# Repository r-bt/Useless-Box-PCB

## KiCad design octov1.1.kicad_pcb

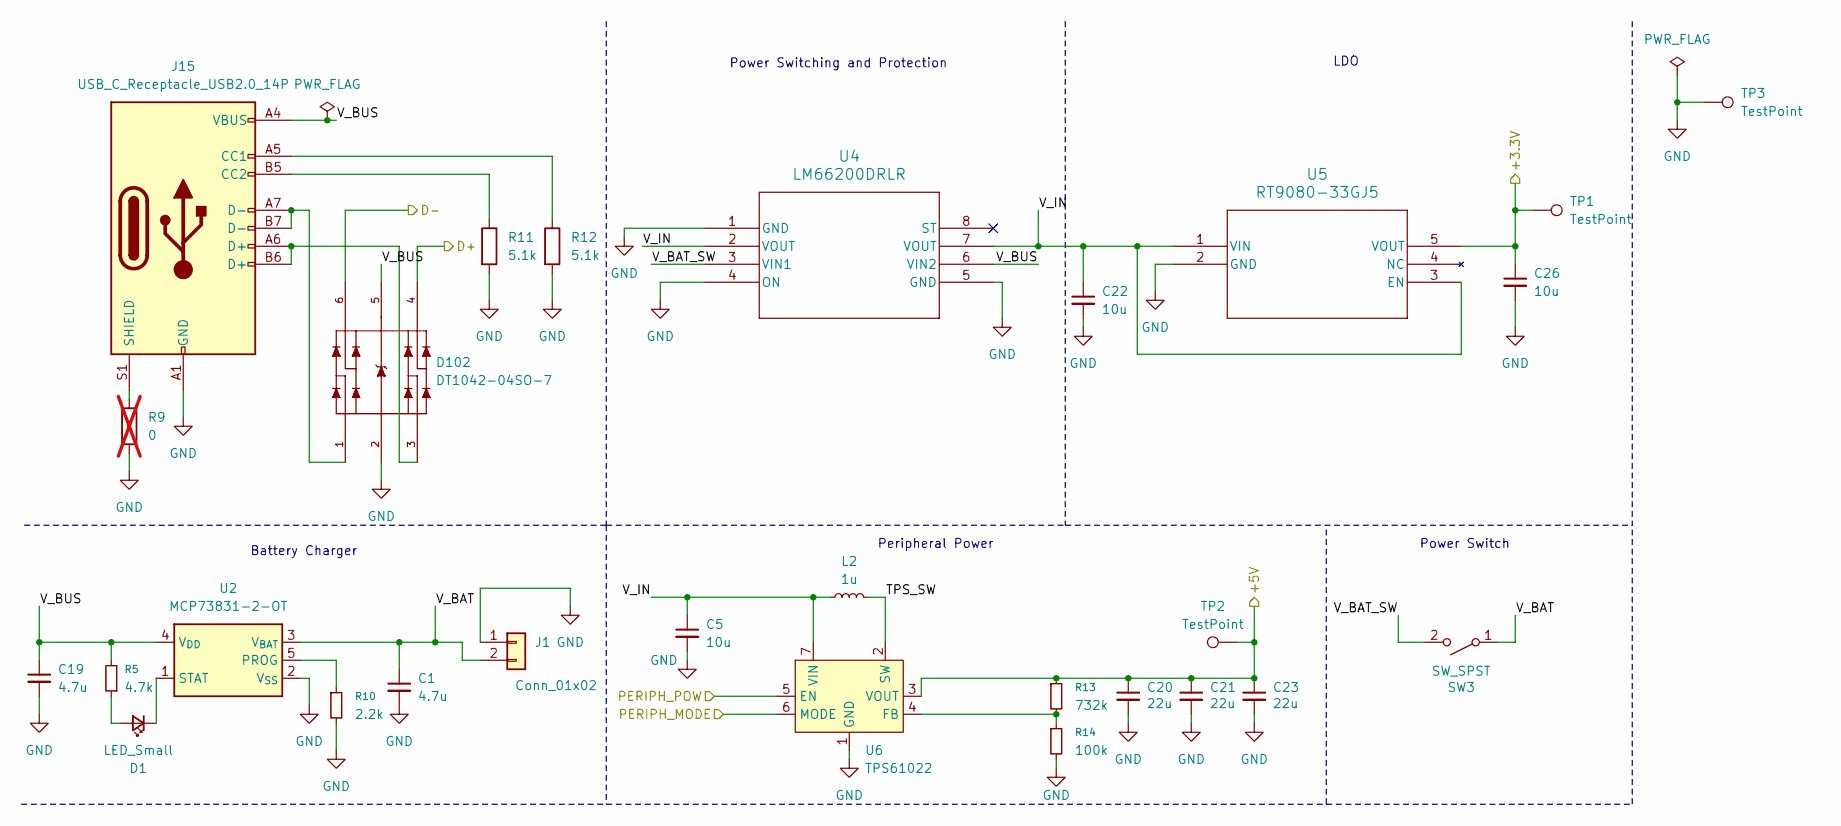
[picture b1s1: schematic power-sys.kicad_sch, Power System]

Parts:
C1, C19: 4.7u; C_0402_1005Metric_small_pads
C5, C22, C26: 10u; C_0402_1005Metric_small_pads
C20, C21, C23: 22u; C_0603_1608Metric
D1: LED_Small; LED_0603_1608Metric
D102: DT1042-04SO-7; SOT-23-6; PARTREV 2-2
J1: Conn_01x02; JST_PH_S2B-PH-K_1x02_P2.00mm_Horizontal
J15: USB_C_Receptacle_USB2.0_14P; USB_C_Receptacle_HRO_TYPE-C-31-M-12
L2: 1u; L_Coilcraft_XAL6030-XXX
R5: 4.7k; R_0402_1005Metric
R9: 0; R_0402_1005Metric; not fitted
R10: 2.2k; R_0402_1005Metric
R11, R12: 5.1k; R_0402_1005Metric
R13: 732k; R_0402_1005Metric
R14: 100k; R_0402_1005Metric
SW3: SW_SPST; JST_XH_S2B-XH-A-1_1x02_P2.50mm_Horizontal
TP1, TP2, TP3: TestPoint; TestPoint_THTPad_D1.5mm_Drill0.7mm
U2: MCP73831-2-OT; SOT-23-5
U4: LM66200DRLR; SOT-583-8
U5: RT9080-33GJ5; TSOT-23-5
U6: TPS61022; Texas_RWU0007A_VQFN-7_2x2mm_P0.5mm

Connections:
+5V: C20.1, C21.1, C23.1, R13.1, TP2.1 (1_1), U6.3 (VOUT); also elsewhere on the board
/MCU/+3.3V: C26.1, TP1.1 (1_1), U5.5 (VOUT); also elsewhere on the board
/MCU/PERIPH_MODE: U6.6 (MODE); also elsewhere on the board
/MCU/SERVO_EN: U6.5 (EN); also elsewhere on the board
/MCU/USB_D+: D102.4; also elsewhere on the board
/MCU/USB_D-: D102.6; also elsewhere on the board
/Power System/TPS_SW: L2.2, U6.2 (SW)
/Power System/V_BAT: C1.1, J1.2, SW3.1 (A), U2.3 (V_{BAT})
/Power System/V_BAT_SW: SW3.2 (B), U4.3 (VIN1)
/Power System/V_BUS: C19.1, D102.5, J15.A4 (VBUS), J15.A9 (VBUS), J15.B4 (VBUS), J15.B9 (VBUS), R5.2, U2.4 (V_{DD}), U4.6 (VIN2)
/Power System/V_IN: C5.1, C22.1, L2.1, U4.2 (VOUT), U4.7 (VOUT), U5.1 (VIN), U5.3 (EN), U6.7 (VIN)
GND: C1.2, C5.2, C19.2, C20.2, C21.2, C22.2, C23.2, C26.2, D102.2, J1.1, J15.A1 (GND), J15.A12 (GND), J15.B1 (GND), J15.B12 (GND), R9.2, R10.2, R11.2, R12.2, R14.2, TP3.1 (1_1), U2.2 (V_{SS}), U4.1 (GND), U4.4 (ON), U4.5 (GND), U5.2 (GND), U6.1 (GND); also elsewhere on the board
unnamed: D1.2 (A), R5.1
unnamed: D1.1 (K), U2.1 (STAT)
unnamed: D102.1, J15.A7 (D-), J15.B7 (D-)
unnamed: D102.3, J15.A6 (D+), J15.B6 (D+)
unnamed: J15.A5 (CC1), R12.1
unnamed: J15.B5 (CC2), R11.1
unnamed: J15.S1 (SHIELD), R9.1
unnamed: R10.1, U2.5 (PROG)
unnamed: R13.2, R14.1, U6.4 (FB)

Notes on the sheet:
Battery Charger
Power Switching and Protection
Power Switch
LDO
Peripheral Power

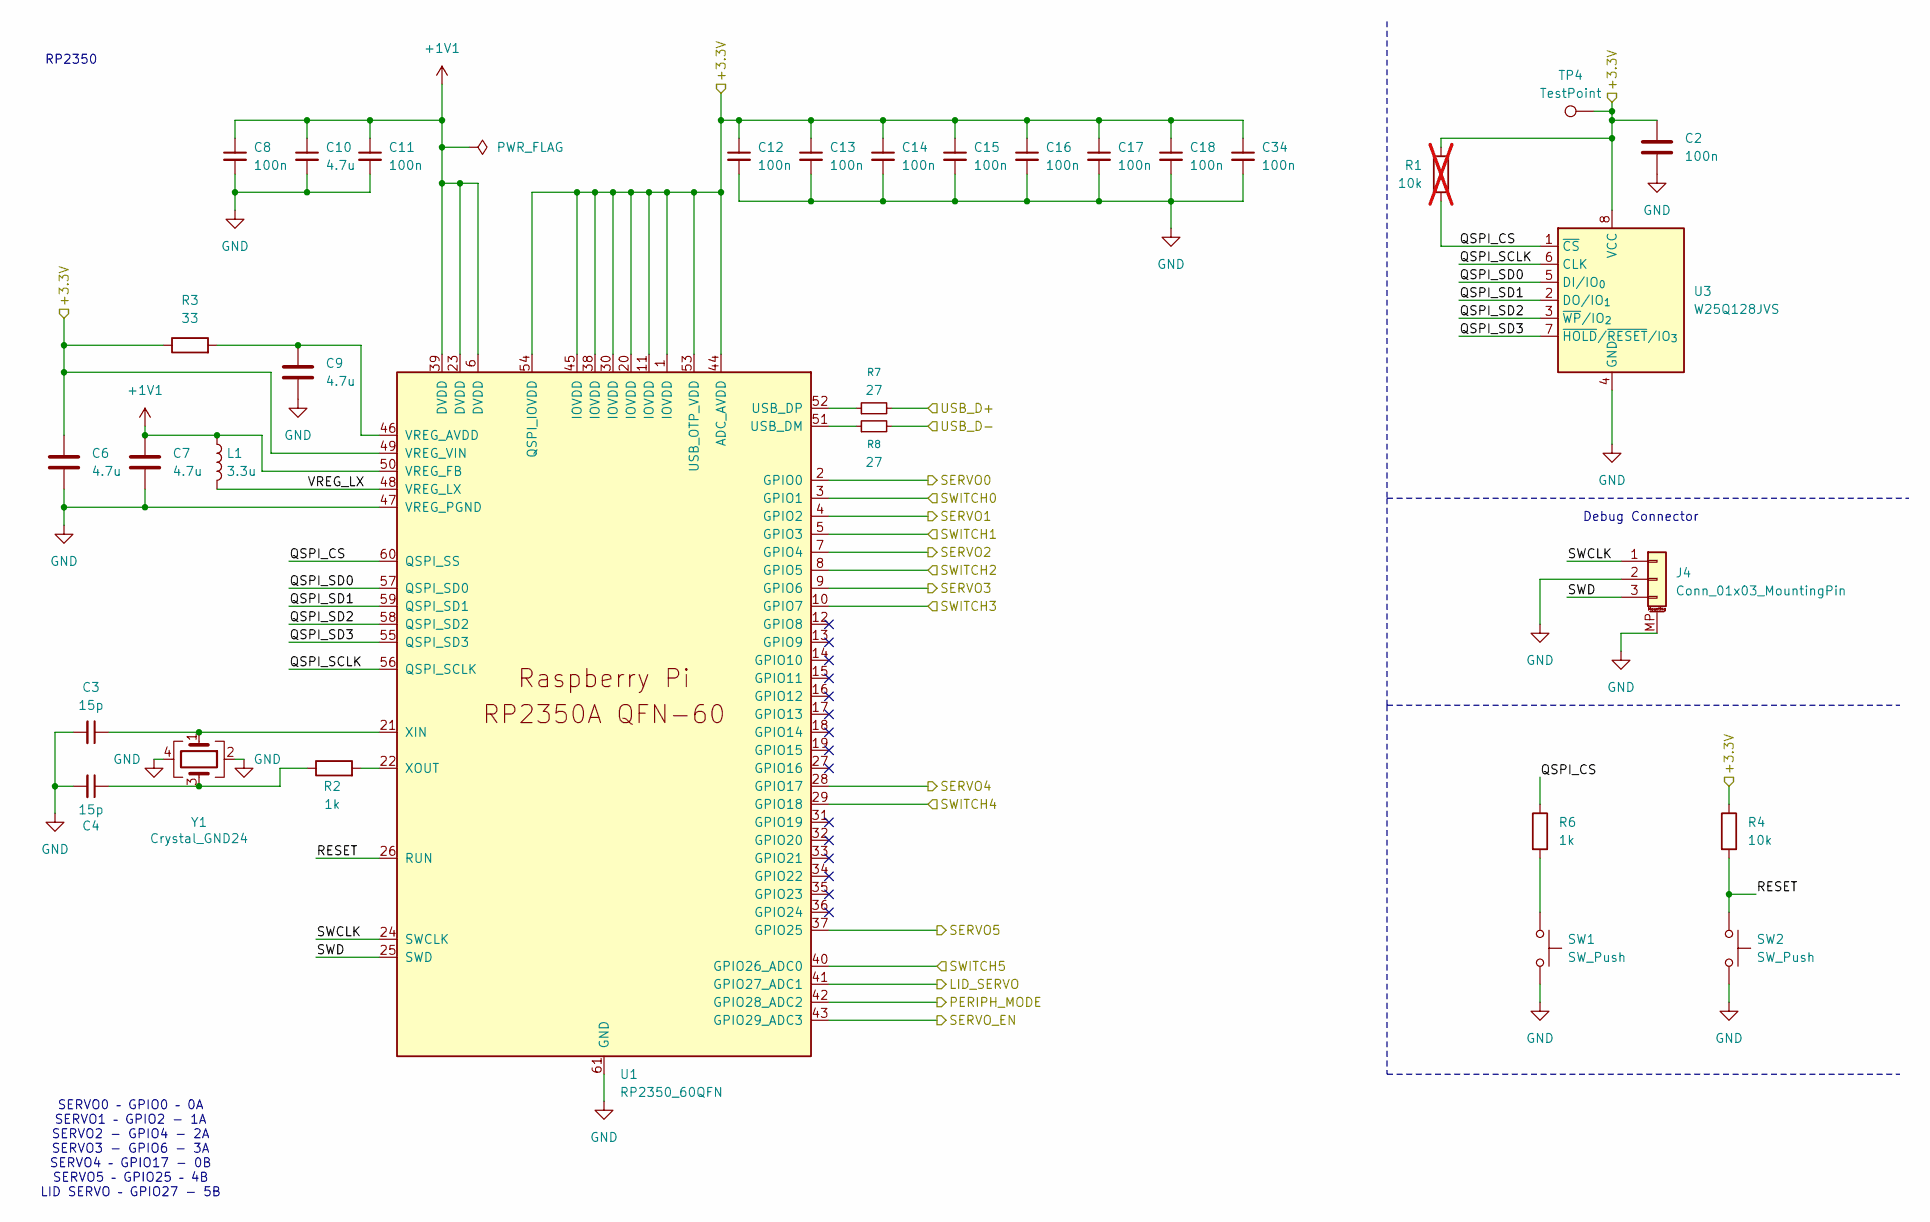
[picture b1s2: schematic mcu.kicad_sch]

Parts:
C2, C8, C11, C12, C13, C14, C15, C16, C17, C18, C34: 100n; C_0402_1005Metric_small_pads
C3, C4: 15p; C_0402_1005Metric_small_pads
C6, C7, C9, C10: 4.7u; C_0402_1005Metric_small_pads
J4: Conn_01x03_MountingPin; JST_SH_BM03B-SRSS-TB_1x03-1MP_P1.00mm_Vertical
L1: 3.3u; L_pol_2016
R1: 10k; R_0402_1005Metric; not fitted
R2, R6: 1k; R_0402_1005Metric
R3: 33; R_0402_1005Metric
R4: 10k; R_0402_1005Metric
R7, R8: 27; R_0603_1608Metric
SW1, SW2: SW_Push; SW_SPST_TS-1088-xR020
TP4: TestPoint; TestPoint_THTPad_D1.5mm_Drill0.7mm
U1: RP2350_60QFN; RP2350-QFN-60-1EP_7x7_P0.4mm_EP3.4x3.4mm_ThermalVias
U3: W25Q128JVS; SOIC-8_5.3x5.3mm_P1.27mm
Y1: Crystal_GND24; Crystal_SMD_3225-4Pin_3.2x2.5mm

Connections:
+1V1: C7.1, C8.1, C10.1, C11.1, L1.1, U1.6 (DVDD), U1.23 (DVDD), U1.39 (DVDD), U1.50 (VREG_FB)
/IO/LID_SERVO: U1.41 (GPIO27_ADC1); also elsewhere on the board
/IO/SERVO0: U1.2 (GPIO0); also elsewhere on the board
/IO/SERVO1: U1.4 (GPIO2); also elsewhere on the board
/IO/SERVO2: U1.7 (GPIO4); also elsewhere on the board
/IO/SERVO3: U1.9 (GPIO6); also elsewhere on the board
/IO/SERVO4: U1.28 (GPIO17); also elsewhere on the board
/IO/SERVO5: U1.37 (GPIO25); also elsewhere on the board
/IO/SWITCH0: U1.3 (GPIO1); also elsewhere on the board
/IO/SWITCH1: U1.5 (GPIO3); also elsewhere on the board
/IO/SWITCH2: U1.8 (GPIO5); also elsewhere on the board
/IO/SWITCH3: U1.10 (GPIO7); also elsewhere on the board
/IO/SWITCH4: U1.29 (GPIO18); also elsewhere on the board
/IO/SWITCH5: U1.40 (GPIO26_ADC0); also elsewhere on the board
/MCU/+3.3V: C2.1, C6.1, C12.1, C13.1, C14.1, C15.1, C16.1, C17.1, C18.1, C34.1, R1.1, R3.1, R4.1, TP4.1 (1_1), U1.1 (IOVDD), U1.11 (IOVDD), U1.20 (IOVDD), U1.30 (IOVDD), U1.38 (IOVDD), U1.44 (ADC_AVDD), U1.45 (IOVDD), U1.49 (VREG_VIN), U1.53 (USB_OTP_VDD), U1.54 (QSPI_IOVDD), U3.8 (VCC); also elsewhere on the board
/MCU/PERIPH_MODE: U1.42 (GPIO28_ADC2); also elsewhere on the board
/MCU/QSPI_CS: R1.2, R6.1, U1.60 (QSPI_SS), U3.1 (~CS)
/MCU/QSPI_SCLK: U1.56 (QSPI_SCLK), U3.6 (CLK)
/MCU/QSPI_SD0: U1.57 (QSPI_SD0), U3.5 (DI/IO_{0})
/MCU/QSPI_SD1: U1.59 (QSPI_SD1), U3.2 (DO/IO_{1})
/MCU/QSPI_SD2: U1.58 (QSPI_SD2), U3.3 (~WP/IO_{2})
/MCU/QSPI_SD3: U1.55 (QSPI_SD3), U3.7 (~HOLD/~RESET/IO_{3})
/MCU/RESET: R4.2, SW2.1, U1.26 (RUN)
/MCU/SERVO_EN: U1.43 (GPIO29_ADC3); also elsewhere on the board
/MCU/SWCLK: J4.1, U1.24 (SWCLK)
/MCU/SWD: J4.3, U1.25 (SWD)
/MCU/USB_D+: R7.2; also elsewhere on the board
/MCU/USB_D-: R8.2; also elsewhere on the board
/MCU/VREG_LX: L1.2, U1.48 (VREG_LX)
GND: C2.2, C3.2, C4.2, C6.2, C7.2, C8.2, C9.2, C10.2, C11.2, C12.2, C13.2, C14.2, C15.2, C16.2, C17.2, C18.2, C34.2, J4.2, J4.MP (MountPin), SW1.2, SW2.2, U1.47 (VREG_PGND), U1.61 (GND), U3.4 (GND), Y1.2, Y1.4; also elsewhere on the board
unnamed: C4.1, R2.1, Y1.3
unnamed: R6.2, SW1.1
unnamed: R8.1, U1.51 (USB_DM)
unnamed: R7.1, U1.52 (USB_DP)
unnamed: C9.1, R3.2, U1.46 (VREG_AVDD)
unnamed: C3.1, U1.21 (XIN), Y1.1
unnamed: R2.2, U1.22 (XOUT)

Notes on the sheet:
RP2350
SERVO0 – GPIO0 – 0A SERVO1 – GPIO2 - 1A SERVO2 - GPIO4 - 2A SERVO3 - GPIO6 - 3A SERVO4 – GPIO17 - 0B SERVO5 – GPIO25 – 4B LID SERVO – GPIO27 - 5B
Debug Connector

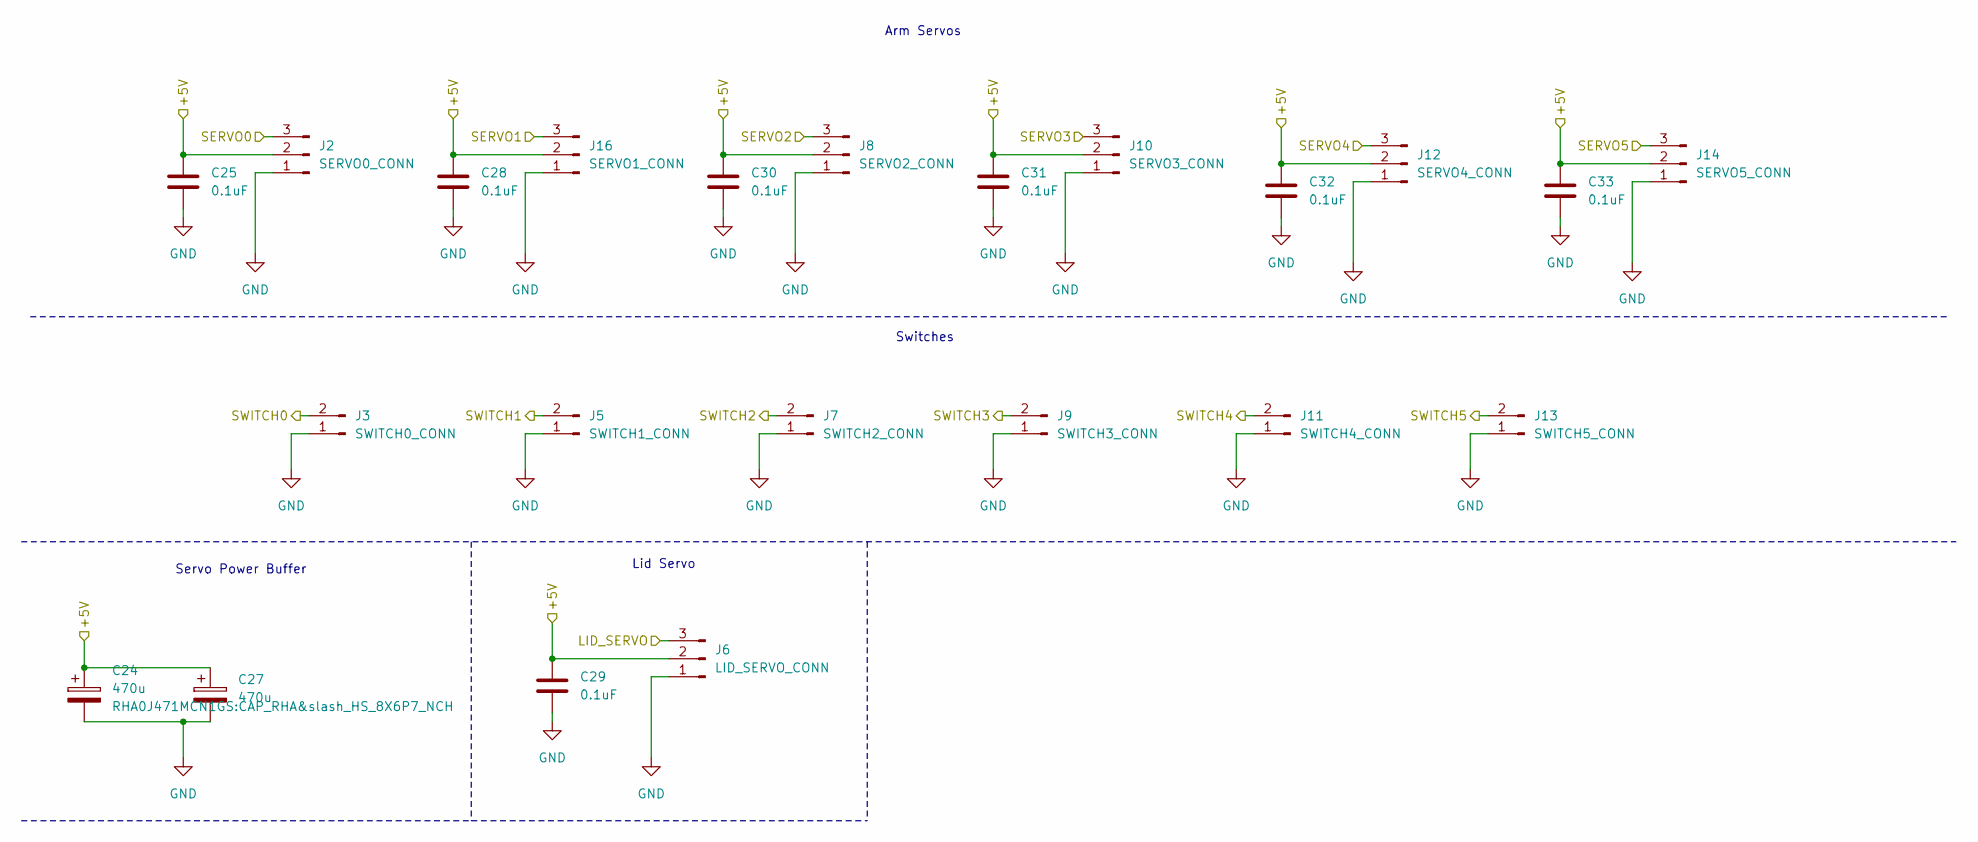
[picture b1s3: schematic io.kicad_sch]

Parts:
C24, C27: 470u; CAP_RHA&slash_HS_8X6P7_NCH
C25, C28, C29, C30, C31, C32, C33: 0.1uF; C_0402_1005Metric_small_pads
J2: SERVO0_CONN; JST_XH_S3B-XH-A-1_1x03_P2.50mm_Horizontal
J3: SWITCH0_CONN; JST_XH_S2B-XH-A-1_1x02_P2.50mm_Horizontal
J5: SWITCH1_CONN; JST_XH_S2B-XH-A-1_1x02_P2.50mm_Horizontal
J6: LID_SERVO_CONN; JST_XH_S3B-XH-A-1_1x03_P2.50mm_Horizontal
J7: SWITCH2_CONN; JST_XH_S2B-XH-A-1_1x02_P2.50mm_Horizontal
J8: SERVO2_CONN; JST_XH_S3B-XH-A-1_1x03_P2.50mm_Horizontal
J9: SWITCH3_CONN; JST_XH_S2B-XH-A-1_1x02_P2.50mm_Horizontal
J10: SERVO3_CONN; JST_XH_S3B-XH-A-1_1x03_P2.50mm_Horizontal
J11: SWITCH4_CONN; JST_XH_S2B-XH-A-1_1x02_P2.50mm_Horizontal
J12: SERVO4_CONN; JST_XH_S3B-XH-A-1_1x03_P2.50mm_Horizontal
J13: SWITCH5_CONN; JST_XH_S2B-XH-A-1_1x02_P2.50mm_Horizontal
J14: SERVO5_CONN; JST_XH_S3B-XH-A-1_1x03_P2.50mm_Horizontal
J16: SERVO1_CONN; JST_XH_S3B-XH-A-1_1x03_P2.50mm_Horizontal

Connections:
+5V: C24.1, C25.1, C27.1, C28.1, C29.1, C30.1, C31.1, C32.1, C33.1, J2.2, J6.2, J8.2, J10.2, J12.2, J14.2, J16.2; also elsewhere on the board
/IO/LID_SERVO: J6.3; also elsewhere on the board
/IO/SERVO0: J2.3; also elsewhere on the board
/IO/SERVO1: J16.3; also elsewhere on the board
/IO/SERVO2: J8.3; also elsewhere on the board
/IO/SERVO3: J10.3; also elsewhere on the board
/IO/SERVO4: J12.3; also elsewhere on the board
/IO/SERVO5: J14.3; also elsewhere on the board
/IO/SWITCH0: J3.2; also elsewhere on the board
/IO/SWITCH1: J5.2; also elsewhere on the board
/IO/SWITCH2: J7.2; also elsewhere on the board
/IO/SWITCH3: J9.2; also elsewhere on the board
/IO/SWITCH4: J11.2; also elsewhere on the board
/IO/SWITCH5: J13.2; also elsewhere on the board
GND: C24.2, C25.2, C27.2, C28.2, C29.2, C30.2, C31.2, C32.2, C33.2, J2.1, J3.1, J5.1, J6.1, J7.1, J8.1, J9.1, J10.1, J11.1, J12.1, J13.1, J14.1, J16.1; also elsewhere on the board

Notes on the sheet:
Arm Servos
Lid Servo
Switches
Servo Power Buffer

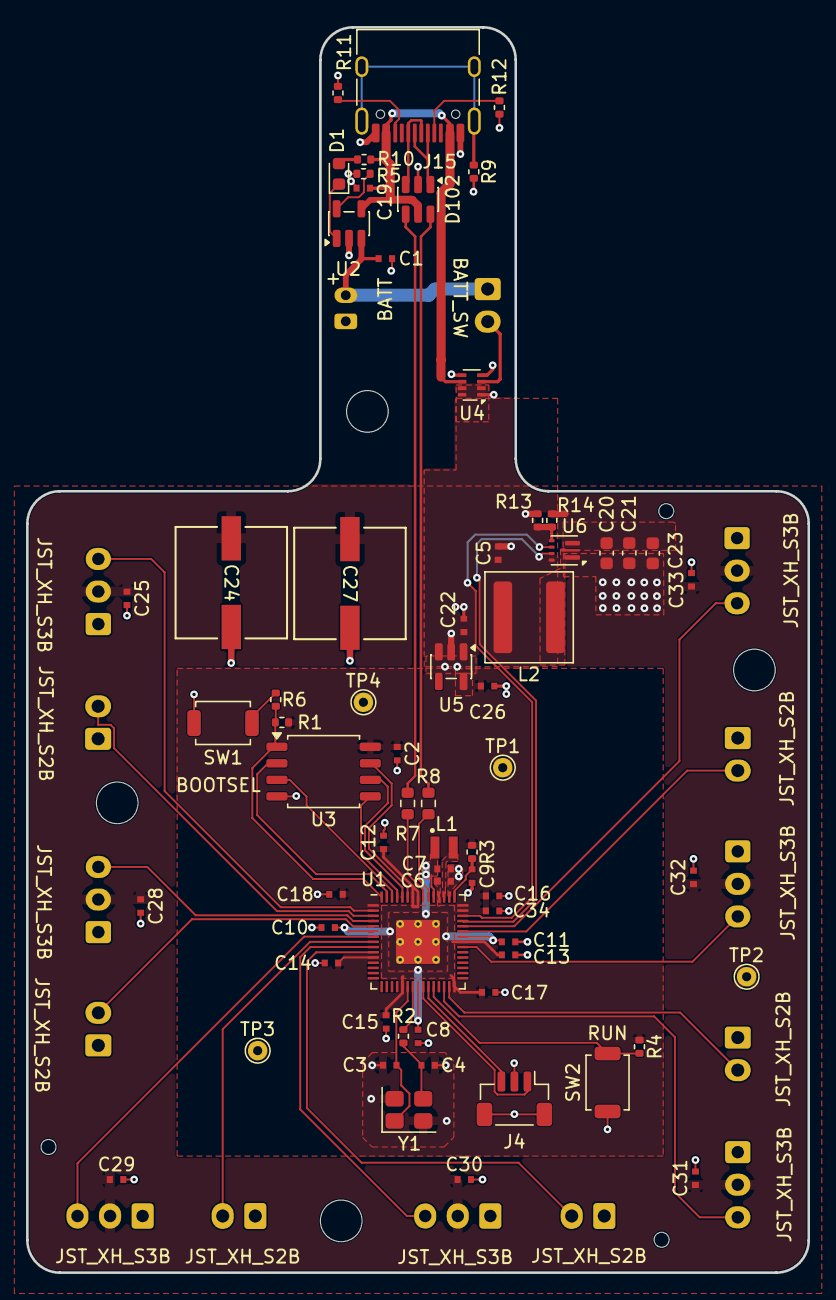
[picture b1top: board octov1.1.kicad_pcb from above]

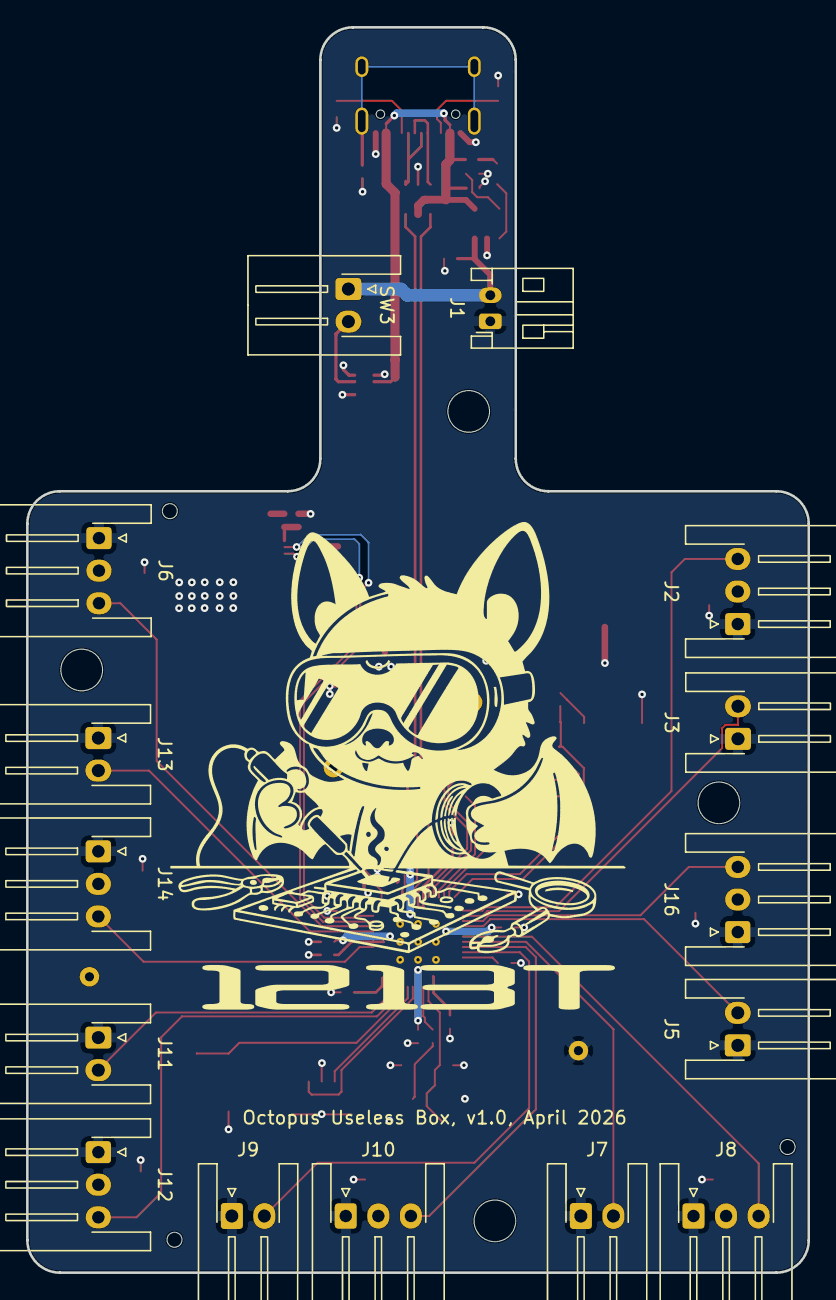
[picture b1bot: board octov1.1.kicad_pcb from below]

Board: 2 copper layers, 60.0 x 95.6 mm, 82 parts (15 on the bottom side), 52 nets.

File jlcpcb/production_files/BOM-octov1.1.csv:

Comment,Designator,Footprint,LCSC,Quantity
0.1uF,"C25,C28,C29,C30,C31,C32,C33",C_0402_1005Metric_small_pads,C1525,7
100k,R14,R_0402_1005Metric,C25741,1
100n,"C11,C12,C13,C14,C15,C16,C17,C18,C2,C34,C8",C_0402_1005Metric_small_pads,C1525,11
10k,"R15,R4",R_0402_1005Metric,C25744,2
10u,"C22,C26,C5",C_0402_1005Metric_small_pads,C15525,3
15p,"C3,C4",C_0402_1005Metric_small_pads,C1548,2
1k,"R2,R6",R_0402_1005Metric,C11702,2
1u,L2,L_Coilcraft_XAL6030-XXX,C2938919,1
2.2k,R10,R_0402_1005Metric,C25879,1
22u,"C20,C21,C23",C_0603_1608Metric,C59461,3
27,"R7,R8",R_0603_1608Metric,C25190,2
3.3u,L1,L_pol_2016,C42411119,1
33,R3,R_0402_1005Metric,C25105,1
4.7k,R5,R_0402_1005Metric,C25900,1
4.7u,"C1,C10,C19,C6,C7,C9",C_0402_1005Metric_small_pads,C23733,6
5.1k,"R11,R12",R_0402_1005Metric,C25905,2
Crystal_GND24,Y1,Crystal_SMD_3225-4Pin_3.2x2.5mm,C20625731,1
DT1042-04SO-7,D102,SOT-23-6,C2844726,1
LED_Small,D1,LED_0603_1608Metric,C2286,1
LM66200DRLR,U4,SOT-583-8,C3235556,1
MCP73831-2-OT,U2,SOT-23-5,C424093,1
RP2350_60QFN,U1,RP2350-QFN-60-1EP_7x7_P0.4mm_EP3.4x3.4mm_ThermalVias,C42411118,1
RT9080-33GJ5,U5,TSOT-23-5,C841192,1
SW_Push,"SW1,SW2",SW_SPST_TS-1088-xR020,C720477,2
TPS61022,U6,Texas_RWU0007A_VQFN-7_2x2mm_P0.5mm,C915088,1
USB_C_Receptacle_USB2.0_14P,J15,USB_C_Receptacle_HRO_TYPE-C-31-M-12,C165948,1
W25Q128JVS,U3,SOIC-8_5.3x5.3mm_P1.27mm,C97521,1

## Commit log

2026-04-17 Finished layout
2026-04-19 Add testpoints
2026-04-21 Fix some bugs in the circuit
